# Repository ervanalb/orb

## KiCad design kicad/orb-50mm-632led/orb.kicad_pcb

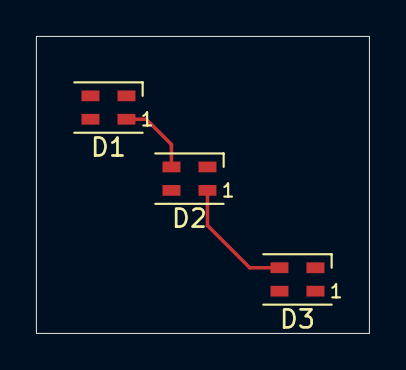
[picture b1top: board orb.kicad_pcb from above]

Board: 2 copper layers, 18.5 x 16.5 mm, 3 parts (0 on the bottom side), 4 nets.

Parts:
D1, D2, D3: SK6805; LED_SK6805_PLCC4_2.4x2.7mm_P1.3mm

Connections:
GND: D1.2 (VSS), D2.2 (VSS), D3.2 (VSS)
unnamed: D1.1 (DOUT), D2.3 (DIN)
unnamed: D2.1 (DOUT), D3.3 (DIN)
VCC: D1.4 (VDD), D2.4 (VDD), D3.4 (VDD)

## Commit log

2024-10-17 First commit--632 LED 50mm sphere
2024-10-17 3332 LED ball--pre-routing
2024-10-22 Routed first board
2024-10-23 Routed half of second board
2024-10-24 Finish routing
2024-10-24 Add text and ANT
2024-10-26 Finish board rev1--add gerbers
